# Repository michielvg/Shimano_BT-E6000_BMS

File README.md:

# Shimano BT-E6000 BMS PCB
My old Shimano BT-E6000 battery gave up on me a couple of years back and I always wanted to check out what killed it. I did not get around to do that and seeing a custom IC on the back of the PCB I got to tracing the hole pcb to try and figure out how it all ticks.

Right now I traced most of it, and the KiCAD project contains a messy schematic file. I hope to continue my work on it, but I wanted to put what I've done on here if I lose interest and perhaps to catch some of the mistakes I've made.

## Notes
### UART message format
PP LL (DD .. DD) CC CC

PP: header, with counter.  
LL: message/data length  
DD: Optional data, according to LL  
CC: Two byte CRC, calculated over all bytes before it.

#### What if first non zero byte is a bitfield?

FROM BATTERY:   
hC1 => 11000001  
h82 => 10000010

FROM CHARGER:  
h41 => 01000001  
h02 => 00000010

FROM DISPLAY:  
h40 => 01000000  

B H ? ? ? ? C C

B: Battery flag ?  
H: Header flag ?  
C: 2 bit message counter ?  

#### FROM BATTERY

h00 h80 h16 h10 h00 h02 h00 h00 h00 hFD h9F h08 h20 hFA h1F h18 h18 h18 ***h5C*** h00 h00 h00 h00 h00 h00 h53 h09 

- 15th data byte could be Battery Level (in %)

#### CRC
The first h00 is not part of the message! It possible could be the end of frame marker see the end of [BATT_RX_ON_BIKE_TIME_OUT_004.txt](RXTXRecords/BATT_RX_ON_BIKE_TIME_OUT_004.txt). The file ends with h00. I framed it wrong from the start.

Not including the first h00 gives me a consistent CRC "CRC-16/IBM-SDLC"

It seems to fit even the headers! Should test a bit more, but the fact that it fits the headers is a big plus.

Great, that's one thing of the checklist.

**cyberchef recipe**  

>Find_/_Replace({'option':'Regex','string':'h'},'',true,false,true,false)
>Fork('\\n','\\n',false)
>From_Hex('Auto')
>CRC_Checksum('CRC-16/IBM-SDLC',{'option':'Decimal','string':'0'},{'option':'Hex','string':'0'},{'option':'Hex','string':'0'},'True','True',{'option':'Hex','string':'0'})

### Varia
- Turning on the battery to check level with led lights on the side triggers a 3.3v pulse on BAT_TX
- Pressing the button on the display unit puts a long pulse of around 6.4v on pins.
- Pressing the button on the display unit puts a 6 second sequence on the BAT_RX pin.

### Possible Charging Initialization

TX Pin on charger provides 3.3V when connected to Battery RX pin.

1. RX at 3.3V to GND ==> comfirmed
2. Q024 (NPN) triggers
3. Q002 (PNP) triggers
4. Battery+ (BAT_P) or Pack+ (PACK_P) via common cathode diode (D004) provide 36v to LDO (IC002)
5. LDO powers MCU (IC003)
6. MCU initializes, but before any communication PIN19 has to go high to take over triggering Q024.

IC003 is constantly powered, System can be bootstrapped by pulling RX high (3.3v)

### Possible Battery Initialization

RX at 3.3V to GND for 6 seconds, after first 280 ms 3 burts of UART message "h00 h40 h00 h21 h49" two next burst come 200ms after eachother.

### IC003

| PIN | DIRECTION | NOTE |
|--|--|--|
| 01 | OUT | Enable led D009
| 02 | OUT | Enable led D008
| 03 | IN (ADC)| Connected to IC001 VOUT, monitors Cell or Pack voltage. 
| 04 | IN (ADC)| Thermistor TH002 - SMD next to MOSFETS
| 05 | IN (ADC)| Thermistor TH003 - Between batteries
| 06 | IN (ADC)| Thermistor TH004 - TH
| 07 | ? | Capacitor to GND
| 08 | ? | Capacitor to GND
| 09 | ? | Capacitor to GND
| 10 | POWER | GND
| 11 |  | NC
| 12 | OUT | Enable Charging
| 13 | OUT | Enable Discharging
| 14 | IN | Connected to IC001 XALERT, L == ALERT
| 15 | ? | Unclear
| 16 | OUT | Enable PACK_P to IC001 PACK pin.
| 17 |  | NC
| 18 | OUT | Enable BAT_P to IC001 PACK pin
| 19 | OUT | Enables BAT_P or PACK_P to LDO (IC002)
| 20 |  | NC
| 21 | OUT | Enable IC001 EEPROM writing
| 22 | OUT | Puts 3.3V on TX of pack (?)
| 23 | IN | Flag to check if TX is high. Possibly used to verify pin 22 or to check if TX is beeing pulled low externally. (?)
| 24 | OUT | Enable led D012
| 25 | POWER | GND
| 26 | POWER | 3.3V
| 27 |  | RX-TX things still to figure out/review
| 28 |  | RX-TX things still to figure out/review
| 29 |  | TP - Unclear
| 30 |  | NC (?)
| 31 |  | RX-TX things still to figure out/review
| 32 |  | RX-TX things still to figure out/review
| 33 | IN | ON/OFF Button
| 34 | OUT | I2C Clock
| 35 | IO | I2C Data
| 36 |  | TP - Unclear
| 37 | OUT  | Enable led D011
| 38 |  | NC
| 39 |  | NC
| 40 |  | NC
| 41 |  | NC
| 42 |  | NC
| 43 |  | NC
| 44 |  | NC
| 45 |  | NC
| 46 |  | NC
| 47 |  | NC
| 48 | OUT | Enable led D010

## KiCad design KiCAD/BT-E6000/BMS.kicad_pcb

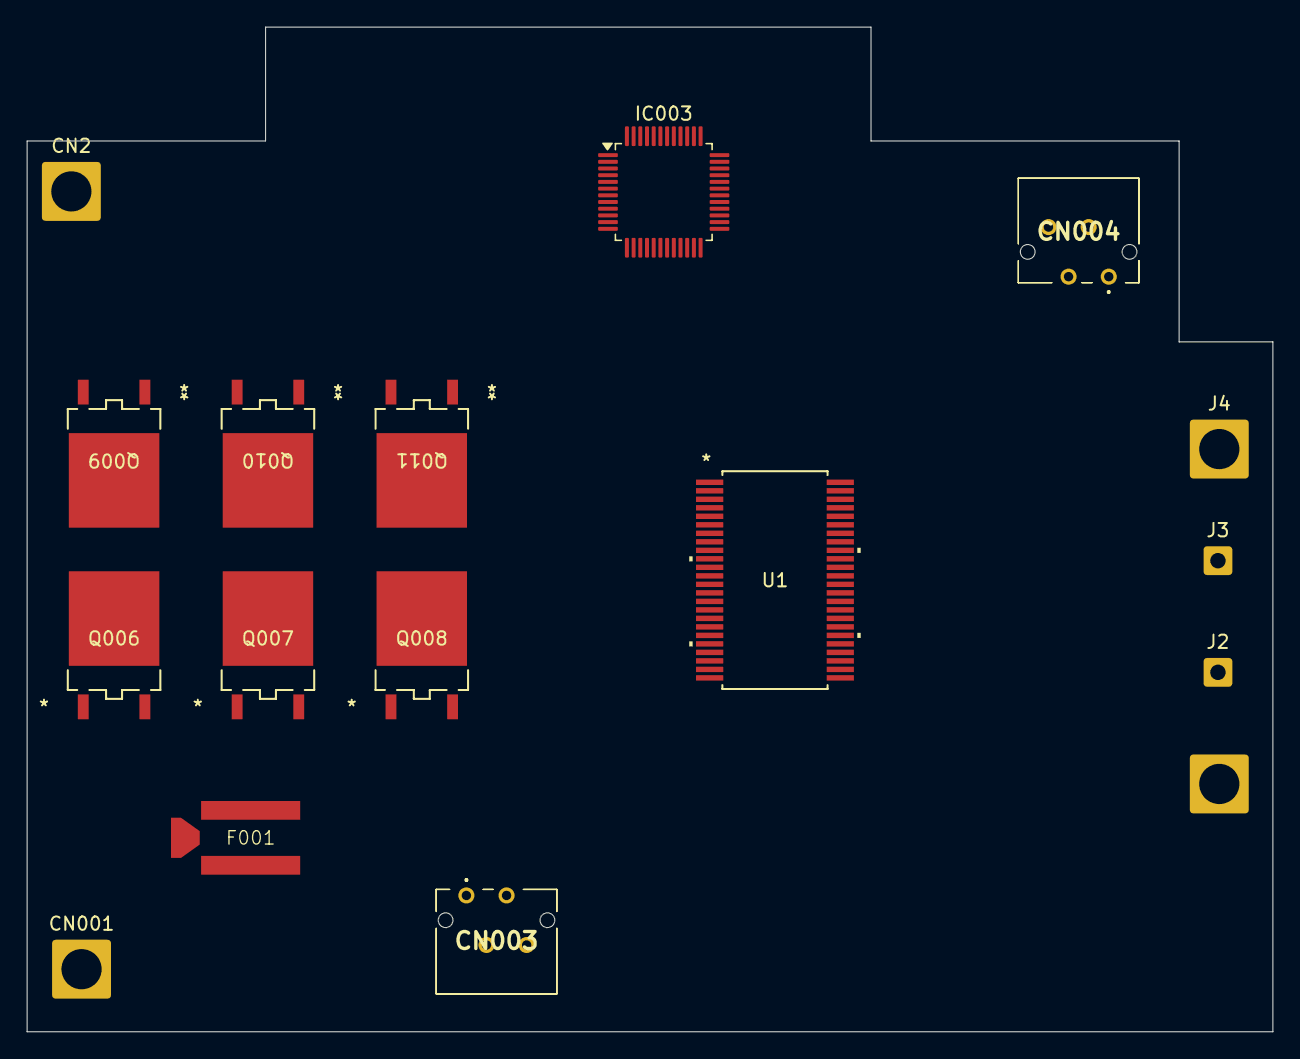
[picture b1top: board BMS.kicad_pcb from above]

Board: 2 copper layers, 93.0 x 75.0 mm, 18 parts (1 on the bottom side), 10 nets, no tracks yet.

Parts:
CN001: CN001; SolderWire-2.5sqmm_1x01_D2.4mm_OD4.4mm
CN2: CN002; SolderWire-2.5sqmm_1x01_D2.4mm_OD4.4mm
CN003, CN004: S04B-ZESK-2D_T__LF__SN_; S04BZESK2DTLFSN
F001: SCF9550
IC002: TPS7A1633DGNT; SOP65P490X110-9N
IC003: R7FS12878xA01CFL; LQFP-48_7x7mm_P0.5mm
J1: -; SolderWire-2.5sqmm_1x01_D2.4mm_OD4.4mm
J2: Rx; SolderWire-0.5sqmm_1x01_D0.9mm_OD2.1mm
J3: Tx; SolderWire-0.5sqmm_1x01_D0.9mm_OD2.1mm
J4: +; SolderWire-2.5sqmm_1x01_D2.4mm_OD4.4mm
Q006, Q007, Q008, Q009, Q010, Q011: ATP304-TL-H; DPAKSINGLE-ATPAK-4_369AM_OSI-M
U1: BQ77PL900DL; DL48-M

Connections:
/BAT_P: CN001.1, F001.2
/CHG_GATES: Q009.1 (G), Q010.1 (G), Q011.1 (G)
/FUSED_BAT_P: F001.1, Q006.3 (S), Q007.3 (S), Q008.3 (S)
/PACK_P: J4.1, Q009.3 (S), Q010.3 (S), Q011.3 (S)
/TIN: U1.38 (TIN), U1.39 (TOUT)
/VLOG: U1.32 (VLOG), U1.40 (VREG2)
GND: F001.3, IC002.4 (GND), J1.1, U1.3 (CP4), U1.21 (GND), U1.29 (IOUT), U1.30 (GND), U1.33 (CNF0), U1.34 (CNF1), U1.35 (CNF2), U1.36 (ZEDE), U1.37 (GND), U1.41 (GND)
unnamed: IC003.6 (VSS), IC003.31 (VSS)
unnamed: Q006.2 (D), Q007.2 (D), Q008.2 (D), Q009.2 (D), Q010.2 (D), Q011.2 (D)
unnamed: Q006.1 (G), Q007.1 (G), Q008.1 (G)

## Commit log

2025-09-03 Added README.md
2025-09-03 Added possible IC003 pinout to README.
2025-09-04 Recorded RX/TX between BATT and CHARGER
2025-09-05 Measured BAT_RX on Display BTN press
2025-09-05 Added missing images
2025-09-05 Added UART message format to README.md
2026-03-19 Seems I did not push everything, and I updated schematic to show CN001 instead of CN002
2026-03-19 Inspiration hit, CRC found.
2026-03-22 added pictures of BT-E6001 BMS PCB and the BMS Protocol Analysis (from AI)
2026-03-22 Report V2
2026-03-23 KiCAD
2026-03-23 sort
2026-03-23 pictures
2026-04-06 Added BT-E80?? images
